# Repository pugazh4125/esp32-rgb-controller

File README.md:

# ESP32 RGB Controller

A custom-designed Bluetooth RGB LED strip controller using the **ESP32-WROOM** module.  
This project is part of my hardware design portfolio under the brand **Serially Wired**.

## 🔧 Features

- **Wireless Control via BLE** using ESP32
- Drives **12V RGB LED Strips** using IRLZ44N MOSFETs
- **Dual Power Input**:
  - USB-C (5V)
  - DC Barrel Jack (12V)
- Onboard **LD1117 3.3V Linear Regulator**
- **CH340N USB-to-Serial Interface** for easy programming
- **Logic Level Shifting** between 5V UART and 3.3V ESP32
- **Onboard LED indicators** for power and status
- Clean silkscreen labels, antenna keepout respected
- Designed in **KiCad** with ERC and DRC error-free

Feel Free to modify or collabrate with me in the project

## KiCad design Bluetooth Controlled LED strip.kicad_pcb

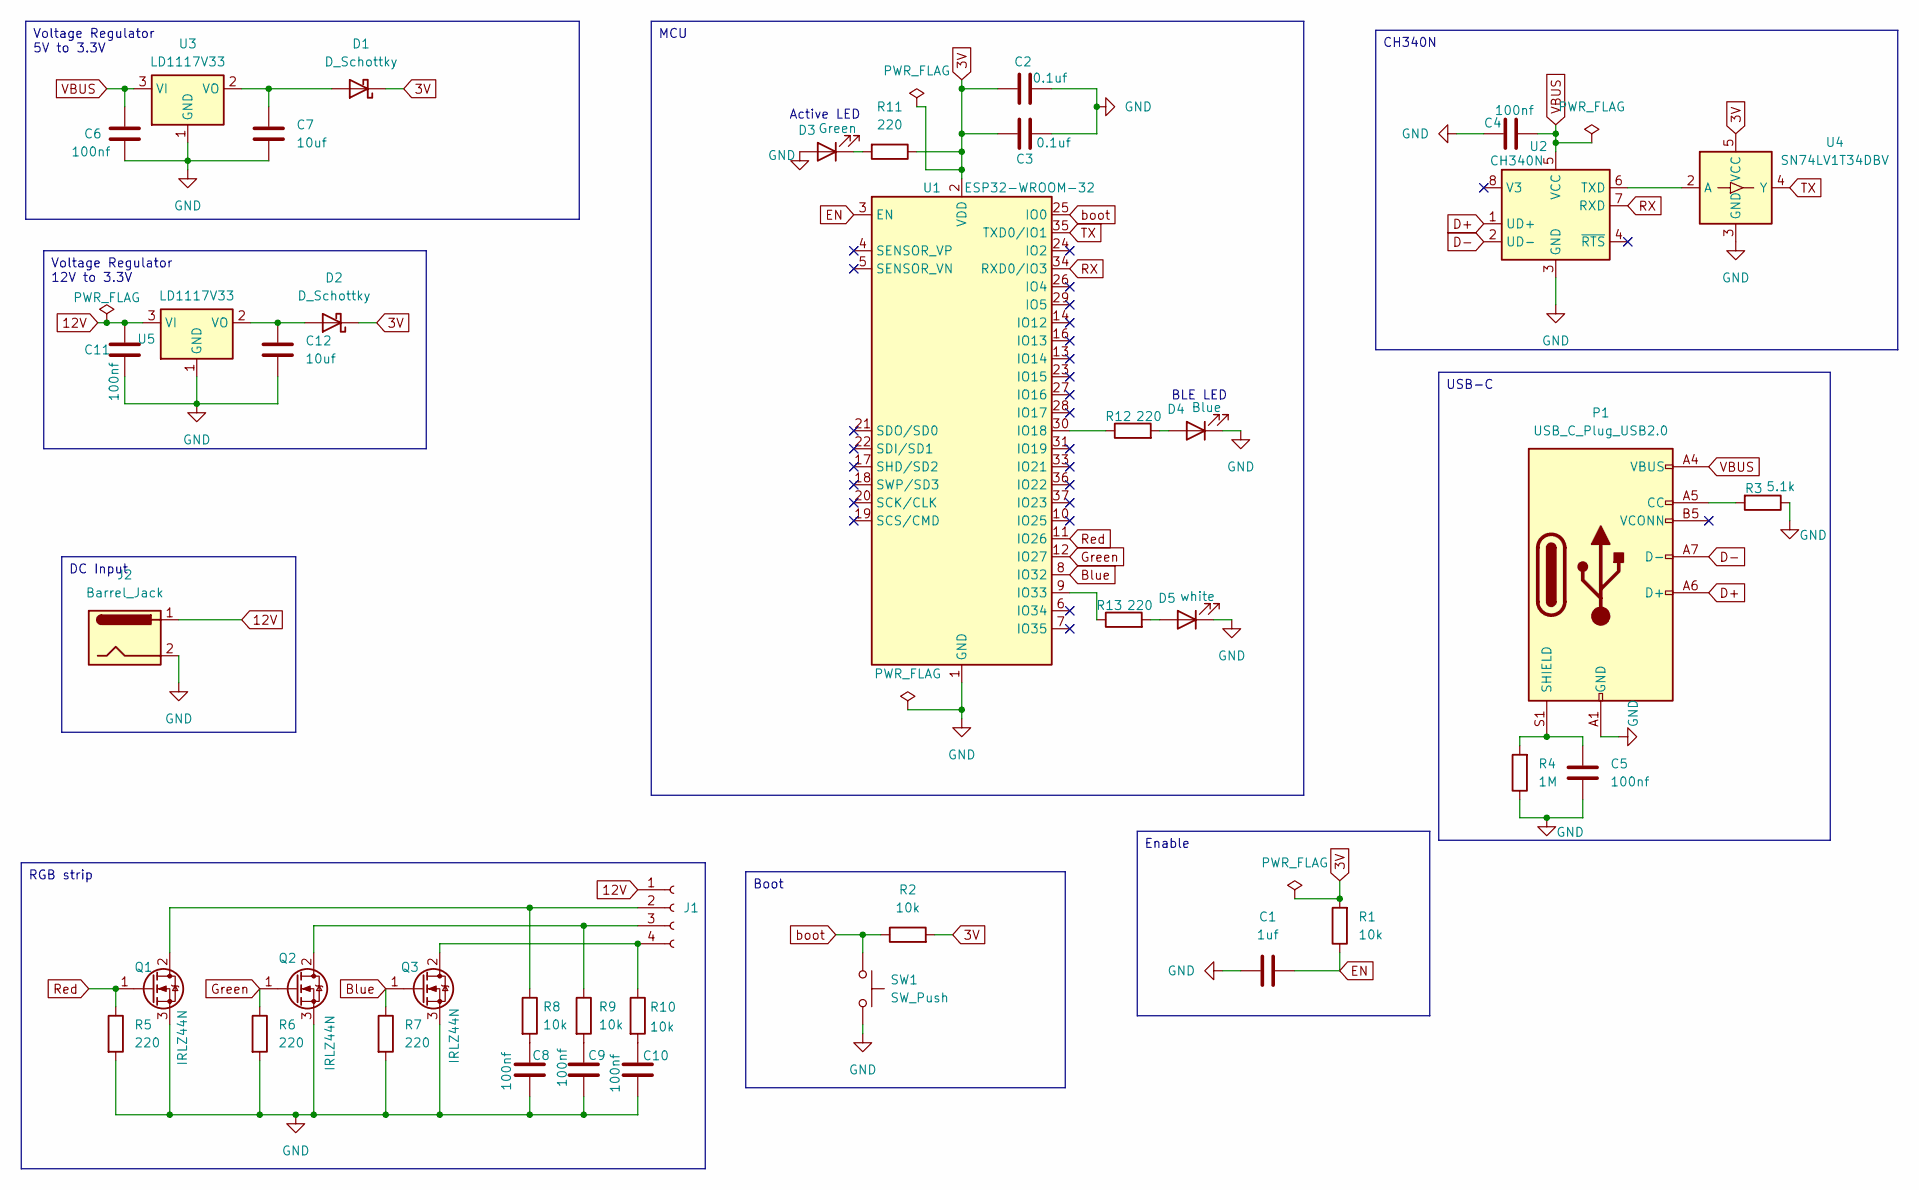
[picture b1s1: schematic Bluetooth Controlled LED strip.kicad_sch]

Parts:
C1: 1uf; C_0603_1608Metric
C2, C3: 0.1uf; C_0603_1608Metric
C4, C5, C6, C8, C9, C10, C11: 100nf; C_0603_1608Metric
C7, C12: 10uf; C_0603_1608Metric
D1, D2: D_Schottky; D_DO-41_SOD81_P10.16mm_Horizontal
D3: Green; LED_0603_1608Metric
D4: Blue; LED_0603_1608Metric
D5: white; LED_0603_1608Metric
J1: Conn_01x04_Socket; PinSocket_1x04_P2.54mm_Vertical
J2: Barrel_Jack; BarrelJack_Wuerth_694108106102_2.5x5.5mm
P1: USB_C_Plug_USB2.0; USB_C_Plug_JAE_DX07P024AJ1
Q1, Q2, Q3: IRLZ44N; TO-220-3_Vertical
R1, R2, R8, R9, R10: 10k; R_Axial_DIN0207_L6.3mm_D2.5mm_P10.16mm_Horizontal
R3: 5.1k; R_Axial_DIN0207_L6.3mm_D2.5mm_P10.16mm_Horizontal
R4: 1M; R_Axial_DIN0207_L6.3mm_D2.5mm_P10.16mm_Horizontal
R5, R6, R7, R11, R12, R13: 220; R_Axial_DIN0207_L6.3mm_D2.5mm_P10.16mm_Horizontal
SW1: SW_Push; SW_PUSH_6mm_H5mm
U1: ESP32-WROOM-32
U2: CH340N; SOP-8_3.9x4.9mm_P1.27mm
U3, U5: LD1117V33; TO-220-3_Vertical
U4: SN74LV1T34DBV; SOT-23-5

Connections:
3V: C2.1, C3.1, D1.1 (K), D2.1 (K), R1.2, R2.2, R11.1, U1.2 (VDD), U4.5 (VCC)
12V: C11.1, J1.1, J2.1, U5.3 (VI)
Blue: Q3.1 (G), R7.1, U1.8 (IO32)
D+: P1.A6 (D+), U2.1 (UD+)
D-: P1.A7 (D-), U2.2 (UD-)
EN: C1.2, R1.1, U1.3 (EN)
GND: C1.1, C2.2, C3.2, C4.1, C5.2, C6.2, C7.2, C8.2, C9.2, C10.2, C11.2, C12.2, D3.2 (A), D4.1 (K), D5.1 (K), J2.2, P1.A1 (GND), P1.A12 (GND), P1.B1 (GND), P1.B12 (GND), Q1.3 (S), Q2.3 (S), Q3.3 (S), R3.1, R4.1, R5.2, R6.2, R7.2, SW1.2, U1.1 (GND), U1.15 (GND), U1.38 (GND), U1.39 (GND), U2.3 (GND), U3.1 (GND), U4.3 (GND), U5.1 (GND)
Green: Q2.1 (G), R6.1, U1.12 (IO27)
unnamed: C8.1, R8.2
unnamed: C9.1, R9.2
unnamed: C10.1, R10.2
unnamed: C7.1, D1.2 (A), U3.2 (VO)
unnamed: C12.1, D2.2 (A), U5.2 (VO)
unnamed: D3.1 (K), R11.2
unnamed: D4.2 (A), R12.2
unnamed: D5.2 (A), R13.2
unnamed: J1.2, Q1.2 (D), R8.1
unnamed: J1.3, Q2.2 (D), R9.1
unnamed: J1.4, Q3.2 (D), R10.1
unnamed: P1.A5 (CC), R3.2
unnamed: C5.1, P1.S1 (SHIELD), R4.2
unnamed: R12.1, U1.30 (IO18)
unnamed: R13.1, U1.9 (IO33)
unnamed: U2.6 (TXD), U4.2 (A)
RX: U1.34 (RXD0/IO3), U2.7 (RXD)
Red: Q1.1 (G), R5.1, U1.11 (IO26)
TX: U1.35 (TXD0/IO1), U4.4 (Y)
VBUS: C4.2, C6.1, P1.A4 (VBUS), P1.A9 (VBUS), P1.B4 (VBUS), P1.B9 (VBUS), U2.5 (VCC), U3.3 (VI)
boot: R2.1, SW1.1, U1.25 (IO0)

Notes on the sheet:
Active LED
BLE LED
CH340N
RGB strip
DC Input
Boot
Voltage Regulator 5V to 3.3V
Enable
MCU
Voltage Regulator 12V to 3.3V
USB-C

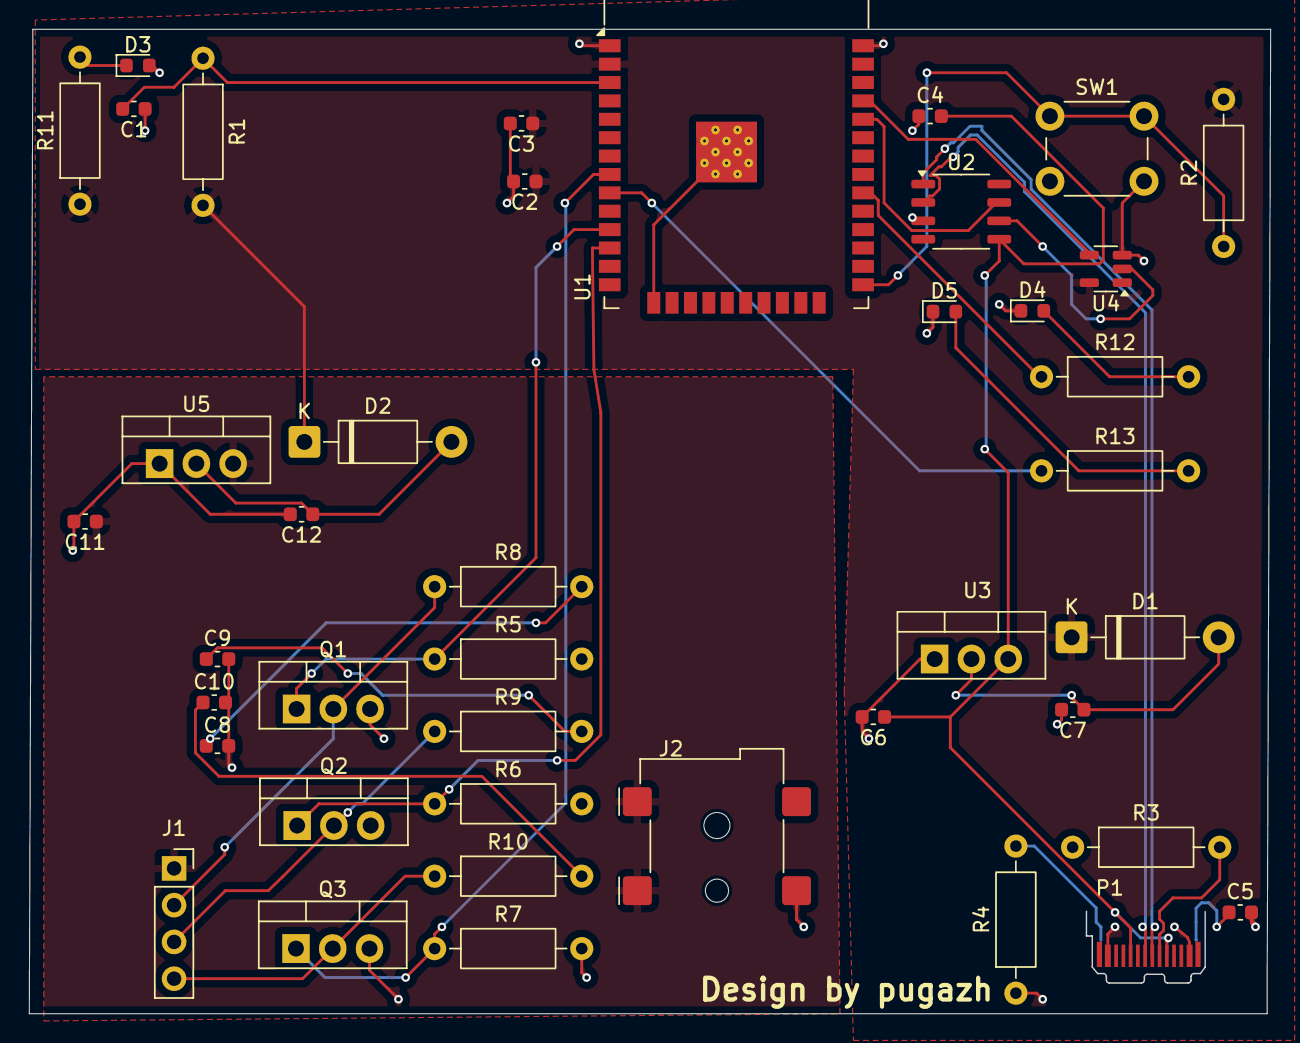
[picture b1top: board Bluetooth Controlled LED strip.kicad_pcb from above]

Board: 2 copper layers, 85.7 x 68.0 mm, 42 parts (0 on the bottom side), 29 nets.
